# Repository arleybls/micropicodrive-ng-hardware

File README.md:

# MicroPicoDrive NG — Hardware

KiCad hardware design for an internal Microdrive replacement for the Sinclair QL. The device emulates a Microdrive cartridge drive using a Raspberry Pi Pico (RP2040) and stores data on a microSD card, fitting in the QL's internal Microdrive bay.

This is an evolution of [gusmanb/micropicodrive](https://github.com/gusmanb/micropicodrive) by Agustín Gimenez Bernad, who reverse-engineered the Microdrive protocol and created the original design. All credit for the core concept and the main board design goes to him.

This repository contains only the hardware. The firmware lives in a separate repository: [micropicodrive-ng-firmware](https://github.com/arleybls/micropicodrive-ng-firmware).

Fitting the board inside a QL — including the Pico and the optional vibration motor — is covered by the [hardware installation manual](docs/HARDWARE_INSTALLATION_MANUAL.md) ([PDF](docs/HARDWARE_INSTALLATION_MANUAL.pdf)). Day-to-day use, SD cards and firmware updates are in the firmware repository's manual.

## What changed in this version

The cartridge board was redesigned around a different user-interface module:

- The I²C SSD1306 OLED was replaced with a 0.96" 80×160 IPS colour display (ST7735S, 4-wire SPI) with four integrated pushbuttons (K1–K4).
- A fourth button and a blinking activity LED were added; the three separate status LEDs were removed.
- The display reset uses a passive RC circuit on the cartridge and the backlight is tied to +3.3V, so the 16-pin edge connector still carries everything with no pins to spare.

The main board is essentially the original MicroPicoDrive design, updated to KiCad 10 format with the edge-connector pinout changes required by the new cartridge.

## Boards

| Board | Folder | Description |
|---|---|---|
| MicroPicoDrive | [MicroPicoDrive/](MicroPicoDrive/) | Main controller board: Raspberry Pi Pico, 5V regulation, level shifters (SN74LVC1T45 ×2, TXU0304), QL Microdrive bus header, edge connector to the cartridge |
| MicroPicoDriveCartridge | [MicroPicoDriveCartridge/](MicroPicoDriveCartridge/) | Cartridge board: microSD socket, ST7735S SPI display with 4 buttons, activity LED, 16-pin edge connector |

Both projects are in KiCad 10 format. Custom symbol and footprint libraries are included alongside each project and referenced with relative paths, so the projects open without extra library setup.

## Assembled boards

Cartridge (left) and main board (right), front side — the cartridge's ST7735S display with the K1–K4 buttons, and the main board's level shifters, cartridge edge-connector slot, and ribbon cable to the QL:

Back side — the cartridge's microSD socket, and the main board with the Raspberry Pi Pico mounted and the motor connector:

## Cartridge panel

A 3D-printable panel fits over the cartridge's display module. It has a window for the screen, openings for the K1–K4 buttons and a slot over the button header. The model is [MicroPicoDriveCartridge/stl/lcd_button_cover_tapered_open.stl](MicroPicoDriveCartridge/stl/lcd_button_cover_tapered_open.stl) (33.5 × 35.5 × 4.4 mm).

Tested print settings:

- Material: matte PLA
- Layer height: 0.2 mm
- Walls: 4

Printed in black and fitted to a cartridge in the drive (left), and rendered in the four colours of the ZX Spectrum rainbow stripe (right):

## Hot-swap guarding

The cartridge can be inserted and removed while the QL is powered, so the edge-connector fingers are staggered to enforce a safe mating order:

- **GND (pin 3) and UI_DETECT (pin 14)** are full length and make contact first. UI_DETECT is tied to GND on the cartridge, so it doubles as a second early ground contact on the opposite face of the board — a tilted insertion finds ground first on either face.
- **+3V3 (pin 1)** is retracted 1 mm and connects second.
- **All signal fingers** are retracted 1.75 mm and connect last, once the cartridge is already referenced and powered. On removal the order reverses: the signals break first while the board still has power, so an interrupted transfer fails cleanly instead of back-powering the display and SD card through their protection diodes.

UI_DETECT is read by the main board (GPIO 15, low = cartridge present). The firmware side of the guard — debouncing the detect signal on insertion before initialising the display and SD card, and tri-stating all cartridge signals on removal — is handled in [micropicodrive-ng-firmware](https://github.com/arleybls/micropicodrive-ng-firmware).

## Fabrication

Gerber and drill files are included for both boards:

- Main board: [MicroPicoDrive/gerbers/](MicroPicoDrive/gerbers/)
- Cartridge: [MicroPicoDriveCartridge/gerbers/](MicroPicoDriveCartridge/gerbers/)

## Bill of materials

Interactive HTML BOMs are provided per board:

- Main board: [MicroPicoDrive/bom/ibom.html](MicroPicoDrive/bom/ibom.html)
- Cartridge: [MicroPicoDriveCartridge/bom/ibom.html](MicroPicoDriveCartridge/bom/ibom.html)

## Credits

- Original MicroPicoDrive hardware, firmware, and Microdrive protocol reverse engineering: [Agustín Gimenez Bernad (gusmanb)](https://github.com/gusmanb)
- SPI display / 4-button cartridge redesign: Arley Silveira

## License

MIT — see [LICENSE](LICENSE). The license retains the original author's copyright notice alongside the notice for the modifications in this repository.

## Related repositories

- [micropicodrive-ng-firmware](https://github.com/arleybls/micropicodrive-ng-firmware) — the firmware that brings these boards to life. It runs on the Pico mounted on the main board and answers the QL's Microdrive bus in real time, serving cartridge images from the microSD card with a menu-driven UI on the cartridge's colour display. Two builds are available: Lite for the standard Pico (RP2040) and Full for the Pico 2 W (RP2350) with Bluetooth and wireless firmware updates. Flash it to the assembled hardware and the QL sees a real Microdrive.
- [sinclair-mdv-builder](https://github.com/arleybls/sinclair-mdv-builder) — a Windows desktop tool (.NET 8 / WPF) to create, inspect, edit, and extract Sinclair QL Microdrive images (`.MDV`). Use it to author or modify cartridge images on your PC — importing files or ZIP archives while preserving QL file metadata — then copy them to the microSD card for this drive to serve to the QL.

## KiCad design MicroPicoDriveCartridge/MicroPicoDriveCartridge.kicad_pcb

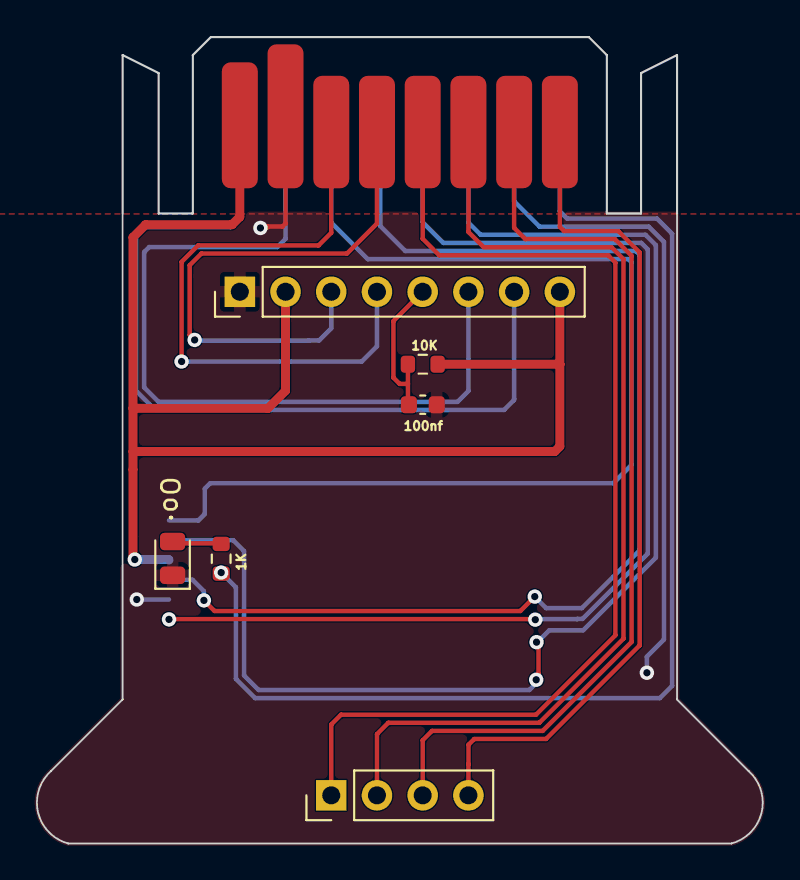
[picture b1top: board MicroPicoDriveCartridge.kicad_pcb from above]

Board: 2 copper layers, 40.3 x 44.8 mm, 8 parts (1 on the bottom side), 17 nets.

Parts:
C1: 100nf; C_0603_1608Metric
D1: LED; LED_0805_2012Metric
J1: Edge Connector; MicroPicoDrive Cartridge Edge
J2: 0.96 IPS ST7735S; PinHeader_1x08_P2.54mm_Vertical
J3: K1..K4; PinHeader_1x04_P2.54mm_Vertical
J4: DM3D-SF; microSD_HC_Hirose_DM3D-SF
R1: 1K; R_0603_1608Metric
R4: 10K; R_0603_1608Metric

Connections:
+3V3: J1.1, J2.2, J2.8, J4.4 (VDD), R4.1
/UI_BTN_BACK: J1.9, J3.1
/UI_BTN_K4: J1.15, J3.4
/UI_BTN_NEXT: J1.11, J3.2
/UI_BTN_SELECT: J1.13, J3.3
/UI_LD_ACTIVITY: J1.16, R1.1
/UI_SCR_CS: J1.2, J2.7
/UI_SCR_DC: J1.4, J2.6
/UI_SCR_MOSI: J1.5, J2.4
/UI_SCR_SCK: J1.7, J2.3
/UI_SD_CS: J1.6, J4.2 (CD/DAT3)
/UI_SD_MISO: J1.10, J4.7 (DAT0)
/UI_SD_MOSI: J1.12, J4.3 (CMD)
/UI_SD_SCK: J1.8, J4.5 (CLK)
GND: C1.2, D1.1 (K), J1.3, J1.14, J2.1, J4.6 (VSS)
unnamed: D1.2 (A), R1.2
unnamed: C1.1, J2.5, R4.2

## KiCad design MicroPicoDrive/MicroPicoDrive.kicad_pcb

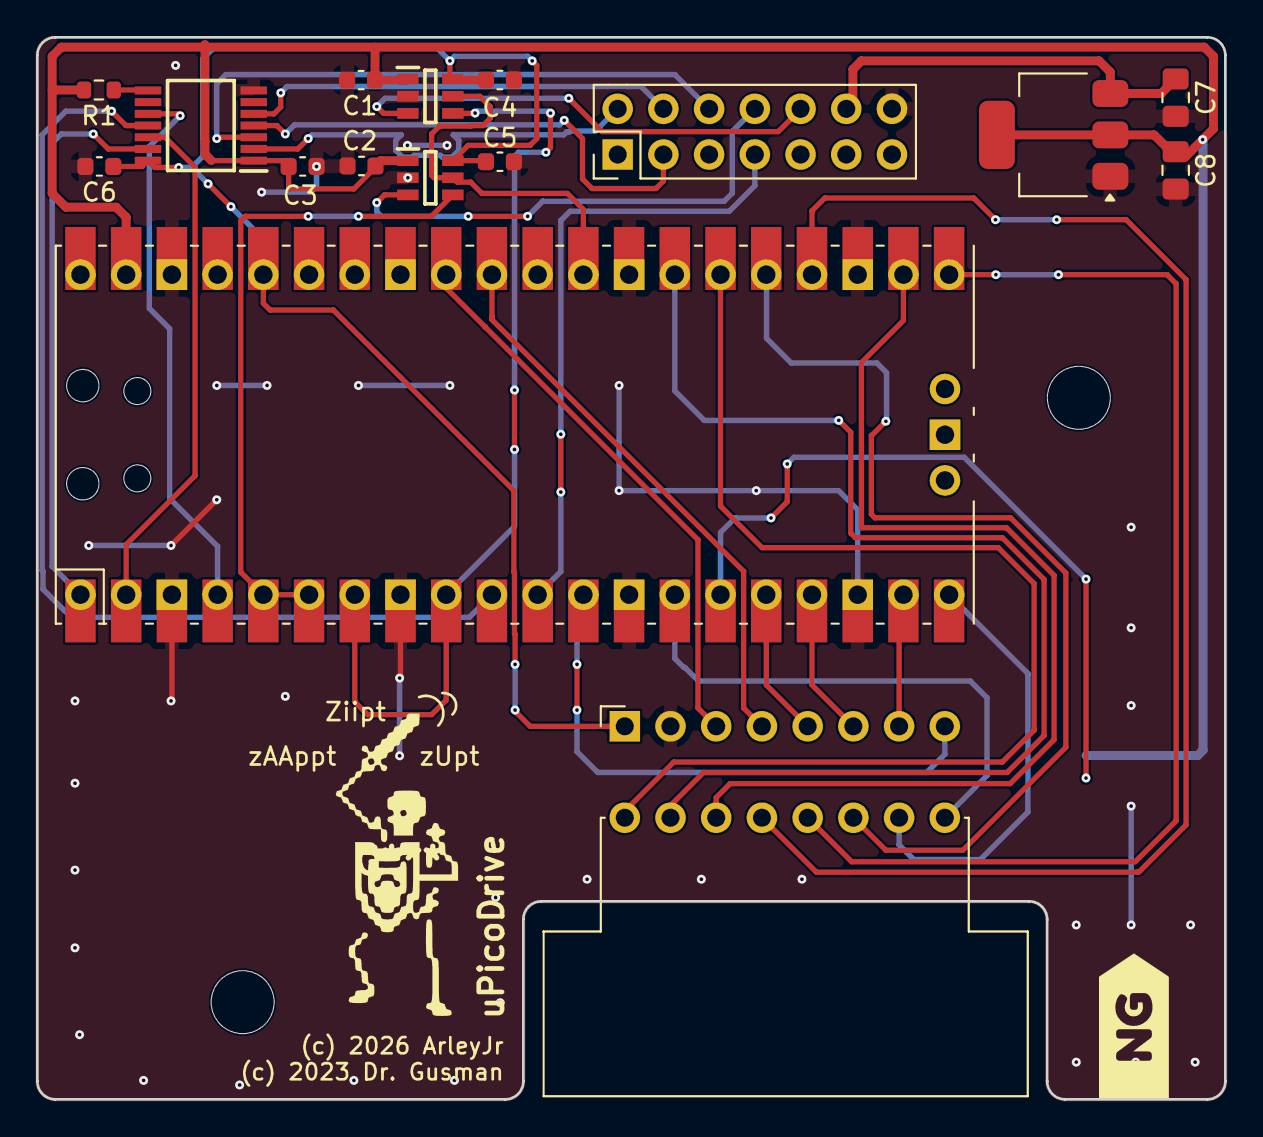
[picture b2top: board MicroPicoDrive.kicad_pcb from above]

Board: 2 copper layers, 66.0 x 59.0 mm, 20 parts (1 on the bottom side), 34 nets.

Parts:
C1, C2, C3, C4, C5, C6: 100nf; C_0603_1608Metric
C7: 10uf; C_0805_2012Metric_Pad1.18x1.45mm_HandSolder
C8: 22uf; C_0805_2012Metric_Pad1.18x1.45mm_HandSolder
IC1, IC2: SN74LVC1T45DBVR; SOT95P280X145-6N
IC3: TXU0304QPWRQ1
J1: Conn_02x16; Edge_connector_02x08
J2: QL_CONN; PinHeader_2x07_P2.54mm_Vertical
J3: PicoBlade-53261-0371; PicoBlade-532610371
MH0, MH1: MountingHole_3.5mm
R1: 4k7; R_0603_1608Metric
U2: Pico; RPi_Pico_SMD_TH
U4: AMS1117-5.0; SOT-223-3_TabPin2
kibuzzard-6A718069: G***; kibuzzard-6A718069

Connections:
+3V3: C4.1, C5.1, C6.1, IC1.6 (VCCB), IC2.6 (VCCB), IC3.14 (VCCB), J1.1, U2.36 (3V3)
+5V: C1.1, C2.1, C3.1, C8.1, IC1.1 (VCCA), IC2.1 (VCCA), IC3.1 (VCCA), J3.2, R1.2, U2.39 (VSYS), U4.2 (VO)
+9V: C7.1, J2.12, U4.3 (VI)
/HEAD_DIR: IC1.5 (DIR), IC2.5 (DIR), U2.29 (GPIO22)
/PICO_CS_CK: IC3.12 (B2Y), U2.2 (GPIO1)
/PICO_CS_IN: IC3.13 (B1Y), U2.1 (GPIO0)
/PICO_CS_OUT: IC3.10 (B4), U2.4 (GPIO2)
/PICO_ERASE: J2.7, U2.11 (GPIO8)
/PICO_HEAD1: IC1.4 (B), U2.5 (GPIO3), U2.6 (GPIO4)
/PICO_HEAD2: IC2.4 (B), U2.7 (GPIO5), U2.9 (GPIO6)
/PICO_R/~W: IC3.11 (B3Y), U2.10 (GPIO7)
/QL_CS_CK: IC3.3 (A2), J2.6
/QL_CS_IN: IC3.2 (A1), J2.2
/QL_CS_OUT: IC3.5 (A4Y), J2.4
/QL_HEAD1: IC1.3 (A), J2.8
/QL_HEAD2: IC2.3 (A), J2.10
/QL_R/~W: IC3.4 (A3), J2.3
/UI_BTN_BACK: J1.9, U2.16 (GPIO12)
/UI_BTN_K4: J1.15, U2.12 (GPIO9)
/UI_BTN_NEXT: J1.11, U2.17 (GPIO13)
/UI_BTN_SELECT: J1.13, U2.19 (GPIO14)
/UI_DETECT: J1.14, U2.20 (GPIO15)
/UI_LD_ACTIVITY: J1.16, U2.14 (GPIO10)
/UI_MOTOR_IN: J3.3, U2.15 (GPIO11)
/UI_SCR_CS: J1.2, U2.26 (GPIO20)
/UI_SCR_DC: J1.4, U2.27 (GPIO21)
/UI_SCR_MOSI: J1.5, U2.32 (GPIO27_ADC1)
/UI_SCR_SCK: J1.7, U2.31 (GPIO26_ADC0)
/UI_SD_CS: J1.6, U2.22 (GPIO17)
/UI_SD_MISO: J1.10, U2.21 (GPIO16)
/UI_SD_MOSI: J1.12, U2.25 (GPIO19)
/UI_SD_SCK: J1.8, U2.24 (GPIO18)
GND: C1.2, C2.2, C3.2, C4.2, C5.2, C6.2, C7.2, C8.2, IC1.2 (GND), IC2.2 (GND), IC3.7 (GND), J1.3, J2.14, J3.1, J3.MP1, J3.MP2, U2.3 (GND), U2.8 (GND), U2.13 (GND), U2.18 (GND), U2.23 (GND), U2.28 (GND), U2.38 (GND), U4.1 (GND)
unnamed: IC3.8 (OE), R1.1

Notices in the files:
MicroPicoDrive/MicroPicoDrive.kicad_pcb:
(c) 2026 ArleyJr
(c) 2023 Dr. Gusman
